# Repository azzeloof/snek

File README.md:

# snek
This is a real hacky snake clone written in verilog over the course of 2.5 days for a game jam. It's designed for the TinyFPGA BX, but it should be easily extendable to other platforms by rewriting top.v.

The game is played via four pushbuttons connected to the FPGA, and video is output over VGA (640x480).

There's a python script (makesplash.py) for generating a splash screen binary from a png image. Just in case you want to replace my beautiful splashscreen art. One note- synthesis takes forever with complicated (not simple geometric) art. For debugging, I recommend commenting out the memory read in spash.v and assigning r, g, and b to 1 or 0. This will result in a simple, solid-color splash screen displayed while you wait for the monitor to realize it has a signal.

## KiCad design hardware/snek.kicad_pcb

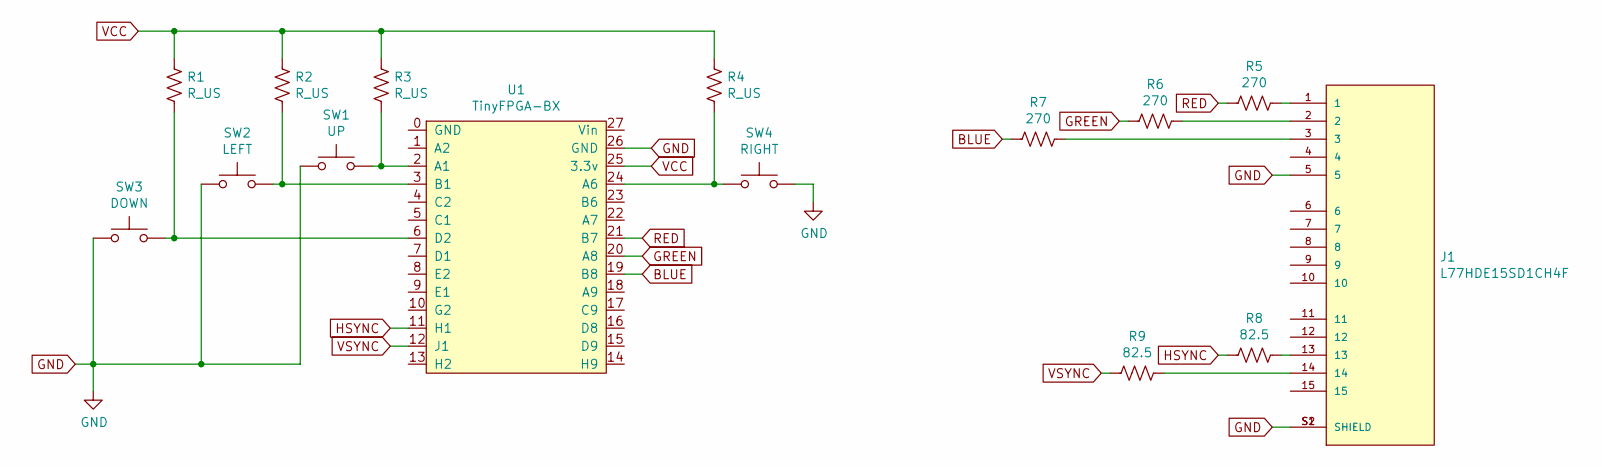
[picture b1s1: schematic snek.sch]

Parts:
J1: L77HDE15SD1CH4F; AMPHENOL_L77HDE15SD1CH4F; PARTREV N/A
R1, R2, R3, R4: R_US; R_Axial_DIN0207_L6.3mm_D2.5mm_P7.62mm_Horizontal
R5, R6, R7: 270; R_Axial_DIN0207_L6.3mm_D2.5mm_P7.62mm_Horizontal
R8, R9: 82.5; R_Axial_DIN0207_L6.3mm_D2.5mm_P7.62mm_Horizontal
SW1: UP; SW_PUSH_6mm
SW2: LEFT; SW_PUSH_6mm
SW3: DOWN; SW_PUSH_6mm
SW4: RIGHT; SW_PUSH_6mm
U1: TinyFPGA-BX

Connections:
BLUE: R7.2, U1.19 (B8)
GND: J1.5, J1.S1 (SHIELD), J1.S2 (SHIELD), SW1.1, SW2.1, SW3.1, SW4.2, U1.26 (GND)
GREEN: R6.2, U1.20 (A8)
HSYNC: R8.2, U1.11 (H1)
unnamed: J1.1, R5.1
unnamed: J1.2, R6.1
unnamed: J1.3, R7.1
unnamed: J1.13, R8.1
unnamed: J1.14, R9.1
unnamed: R1.2, SW3.2, U1.6 (D2)
unnamed: R2.2, SW2.2, U1.3 (B1)
unnamed: R3.2, SW1.2, U1.2 (A1)
unnamed: R4.2, SW4.1, U1.24 (A6)
RED: R5.2, U1.21 (B7)
VCC: R1.1, R2.1, R3.1, R4.1, U1.25 (3.3v)
VSYNC: R9.2, U1.12 (J1)

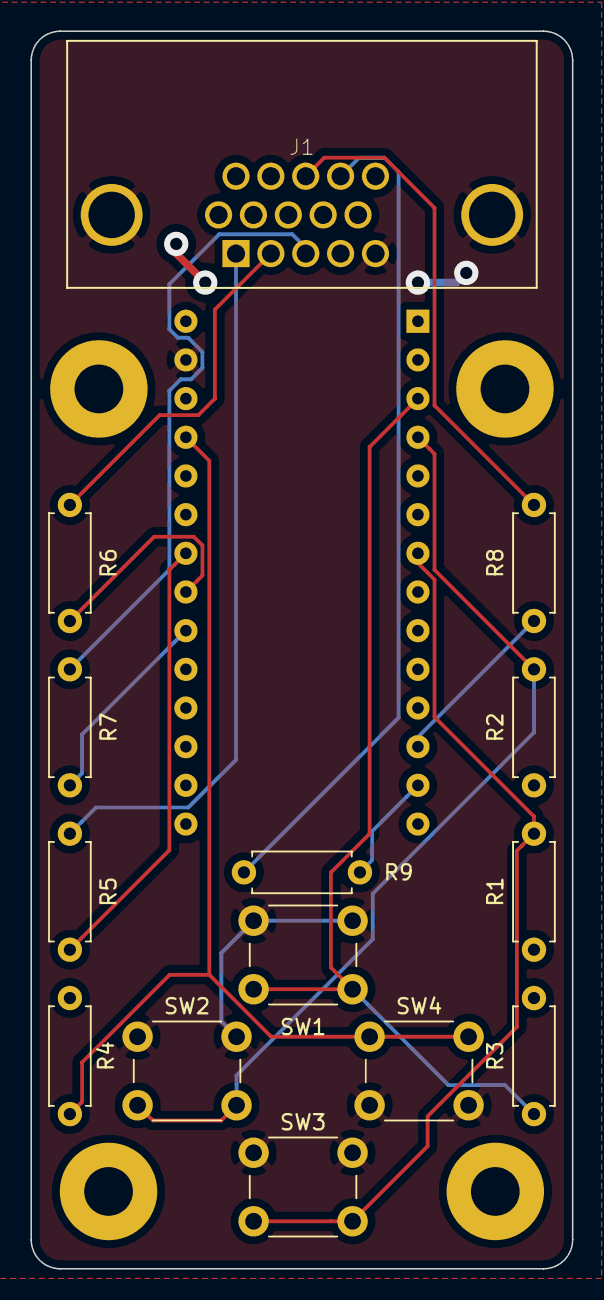
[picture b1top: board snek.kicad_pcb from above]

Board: 2 copper layers, 35.6 x 81.3 mm, 15 parts (1 on the bottom side), 16 nets.

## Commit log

2020-11-27 stuff happened
2020-11-27 it do work
2020-11-28 documented the snek
2020-11-28 sped up, fided food generation bugs
2020-11-29 Cleaned glitches from splash screen with pipeline and streaming RGB.
2020-11-29 designed a PCB for some reason
2020-11-29 cleanup
2020-11-29 splash: green background and yellow foreground.
2020-11-30 cleaned up KiCad files
2020-12-08 fixed visual artifacts, restructured
2020-12-08 Updated 3d printed case
